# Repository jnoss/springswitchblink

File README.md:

# springswitchblink
PCB design files for a board using a spring switch and an attiny85 to blink an LED

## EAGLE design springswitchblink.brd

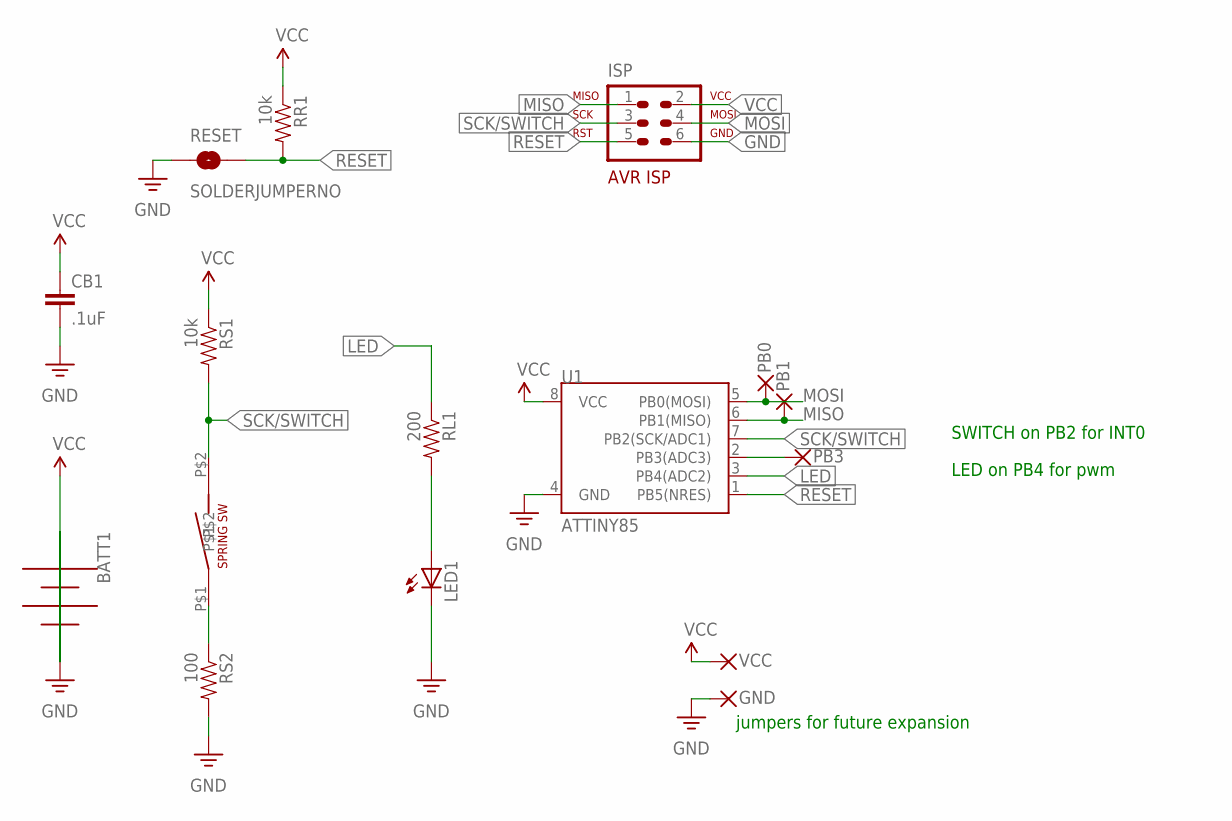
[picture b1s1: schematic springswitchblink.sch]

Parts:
BATT1: AAAMPD-BC2AAAPC; MPD-BC2AAAPC
CB1: .1uF; 0603-CAP
GND: VIAPADVIAPAD; VIAPAD13MIL
ISP: MYISP-AVR-ISP-6VERT; NOSS_AVR-ISP-6
LED1: LED5MM
PB0, PB1, PB3: VIAPADVIAPAD; VIAPAD13MIL
RESET: SOLDERJUMPERNO; SJ_2S-NO
RL1: 200; 0603-RES
RR1: 10k; 0603-RES
RS1: 10k; 0603-RES
RS2: 100; 0603-RES
S1: SPRING_SWITCH; SW-18020P-RA
U1: ATTINY85; SO08-EIAJ
VCC: VIAPADVIAPAD; VIAPAD13MIL

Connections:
GND: BATT1.- (+), CB1.2, GND.1, ISP.6, LED1.K (C), RESET.1, RS2.2, U1.4 (GND)
LED: RL1.1, U1.3 (PB4(ADC2))
MISO: ISP.1, PB1.1, U1.6 (PB1(MISO))
MOSI: ISP.4, PB0.1, U1.5 (PB0(MOSI))
unnamed: LED1.A, RL1.2
unnamed: RS2.1, S1.P$1
unnamed: PB3.1, U1.2 (PB3(ADC3))
RESET: ISP.5, RESET.2, RR1.2, U1.1 (PB5(NRES))
SCK/SWITCH: ISP.3, RS1.2, S1.P$2, U1.7 (PB2(SCK/ADC1))
VCC: BATT1.+ (-), CB1.1, ISP.2, RR1.1, RS1.1, U1.8 (VCC), VCC.1

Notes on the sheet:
SWITCH on PB2 for INT0
jumpers for future expansion
LED on PB4 for pwm

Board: 2 copper layers, 16 parts (1 on the bottom side), 10 nets, no tracks yet.

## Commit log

2016-08-23 initial commit spring switch blink board
2016-08-23 add eagle preview autogen
2016-08-23 test to generate preview
2016-08-23 move back to generate diff
2016-08-25 use libary part for sw-18020p
2016-08-25 use keystone 2466 AAA holder
2016-08-26 rearrange board
2016-08-30 gitignore eagle.epf
2016-08-30 use coin cell 2032
2016-08-30 place and route
2016-08-30 add readme
2016-09-20 reorg and use plcc rgb
2016-09-20 route
2016-09-21 allow option of longer spring switch
2016-09-22 rework, and change outline
2016-09-22 edit board
2016-09-28 board as printed
2016-09-28 add pdf of board and bom csv
2016-09-28 minor reroute
2016-10-03 add gerber paste layer
2016-10-03 add gerbers
2016-10-03 add stencil
2018-04-25 edit labels
2018-04-25 add intermediate step in stencil
2018-04-25 rework original to 2xAAA

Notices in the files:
parts and their libraries:
SparkFun-Capacitors: Licensing: CC v3.0 Share-Alike You are welcome to use this library for commercial purposes.
